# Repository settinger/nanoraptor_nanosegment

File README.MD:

# The NanoRaptor NanoSegment

## Experiments in miniature 7-segment displays

### Sam Ettinger, November 2022

Like many good projects, this started with [a prank tweet:](https://twitter.com/NanoRaptor/status/1483962337334022145)

Like many others, I immediately got sucked into hypotheticals, wondering what it would take to make one of these IRL. Some 0201-sized LEDs in a 7-segment arrangement could fit in an 0805-ish footprint, right?

There are three KiCad projects in the `kicad/` folder:
- `6pin_7seg_0806`, the first version. It's just a panelized PCB with no schematic and some, shall we say, unique features (TODO: explain)
- `6pin_7seg_0806_display_board`. Once the 6-pin 0806 modules are assembled, the modules can be soldered to this board and controlled with an ATtiny84. There are some unused 0805 footprints nearby the modules, which I thought would contribute to it looking like a "real" component.
- `nanoraptor_nanosegment`, my current idea. I want to see if I can fold up an OSH Park flex PCB into a 1208-size footprint with just two pins, like in the original tweet.

TODO: finish this

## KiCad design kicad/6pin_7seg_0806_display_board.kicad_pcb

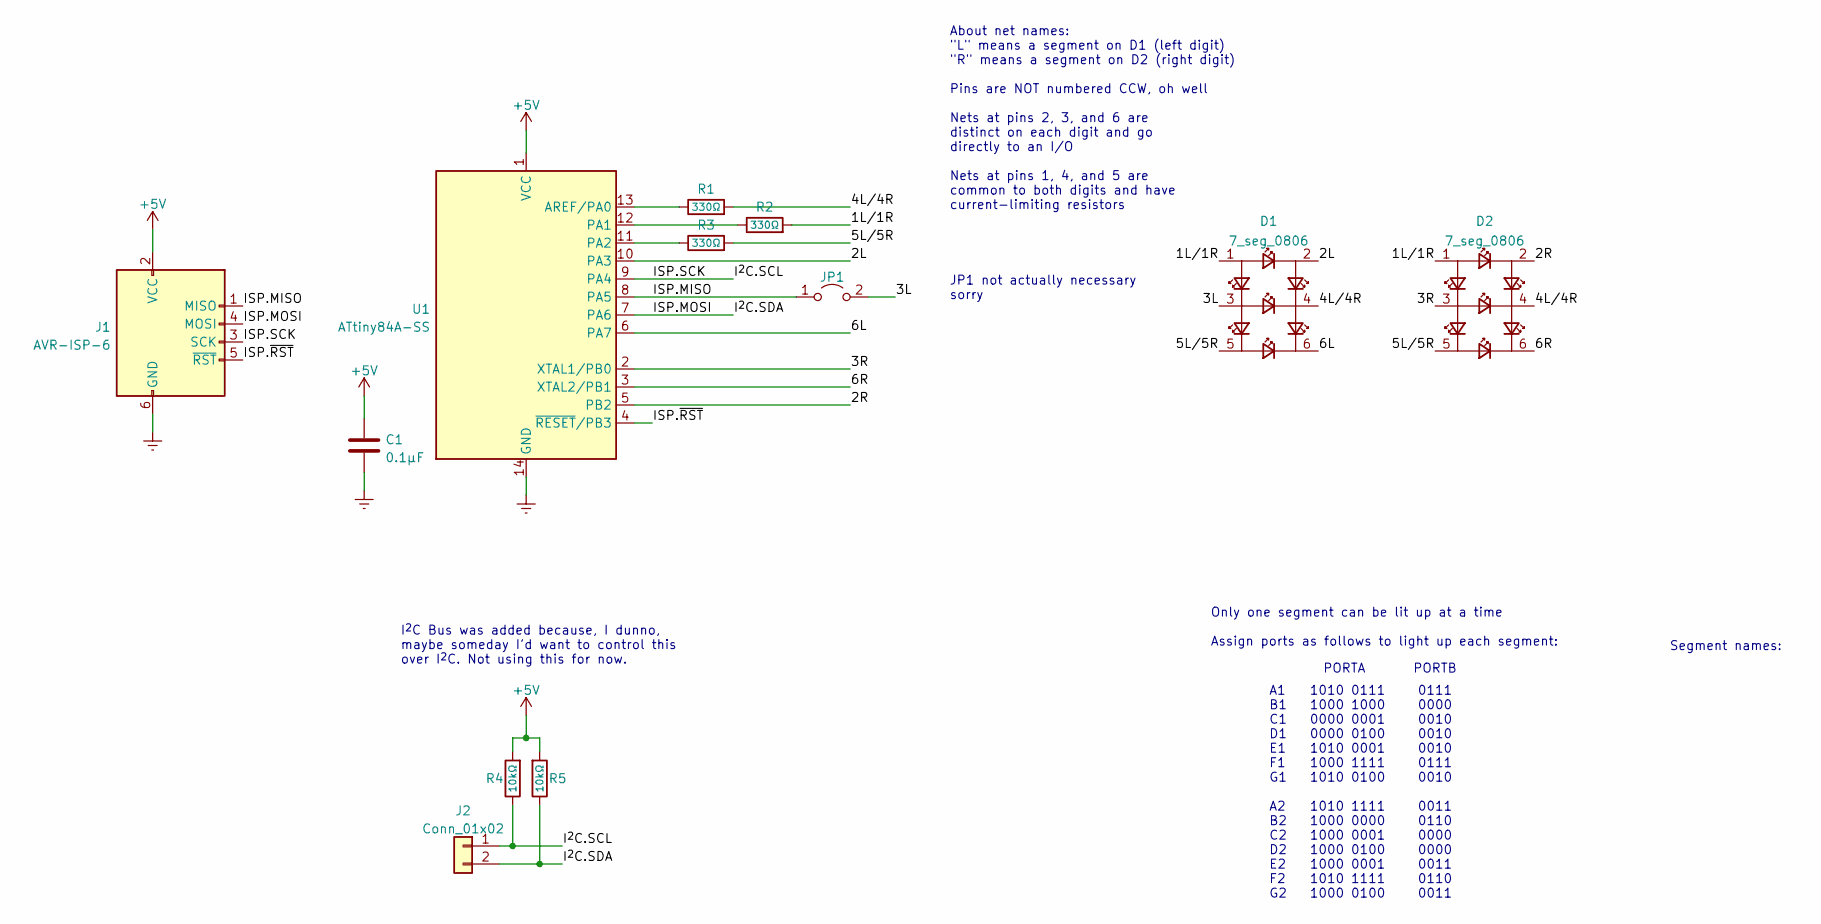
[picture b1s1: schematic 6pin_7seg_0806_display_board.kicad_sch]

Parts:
C1: 0.1μF; C_0805_2012Metric
D1, D2: 7_seg_0806; 7seg_land_pattern
J1: AVR-ISP-6; IDC_header_2x03_P2.54mm_edge-mount
J2: Conn_01x02; PinSocket_1x02_P2.54mm_Vertical
JP1: Jumper_2_Open; SolderJumper-2_P1.3mm_Open_RoundedPad1.0x1.5mm
R1, R2, R3: 330Ω; R_0805_2012Metric
R4, R5: 10kΩ; R_0805_2012Metric
U1: ATtiny84A-SS; SOIC-14_3.9x8.7mm_P1.27mm

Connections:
+5V: C1.1, J1.2 (VCC), R4.2, R5.2, U1.1 (VCC)
/1L/1R: D1.1 (A+F+), D2.1 (A+F+), R2.2
/2L: D1.2 (A-B+), U1.10 (PA3)
/2R: D2.2 (A-B+), U1.5 (PB2)
/3L: D1.3 (E+F-G+), JP1.2 (B)
/3R: D2.3 (E+F-G+), U1.2 (XTAL1/PB0)
/4L/4R: D1.4 (B-C+G-), D2.4 (B-C+G-), R1.2
/5L/5R: D1.5 (D+E-), D2.5 (D+E-), R3.2
/6L: D1.6 (C-D-), U1.6 (PA7)
/6R: D2.6 (C-D-), U1.3 (XTAL2/PB1)
/ISP.MISO: J1.1 (MISO), JP1.1 (A), U1.8 (PA5)
/ISP.MOSI: J1.4 (MOSI), J2.2, R5.1, U1.7 (PA6)
/ISP.SCK: J1.3 (SCK), J2.1, R4.1, U1.9 (PA4)
/ISP.~RST: J1.5 (~RST), U1.4 (~RESET/PB3)
GNDREF: C1.2, J1.6 (GND), U1.14 (GND)
unnamed: R1.1, U1.13 (AREF/PA0)
unnamed: R2.1, U1.12 (PA1)
unnamed: R3.1, U1.11 (PA2)

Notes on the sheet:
1010 0111 1000 1000 0000 0001 0000 0100 1010 0001 1000 1111 1010 0100 1010 1111 1000 0000 1000 0001 1000 0100 1000 0001 1010 1111 1000 0100
JP1 not actually necessary sorry
About net names: "L" means a segment on D1 (left digit) "R" means a segment on D2 (right digit) Pins are NOT numbered CCW, oh well Nets at pins 2, 3, and 6 are distinct on each digit and go directly to an I/O Nets at pins 1, 4, and 5 are common to both digits and have current-limiting resistors
A1 B1 C1 D1 E1 F1 G1 A2 B2 C2 D2 E2 F2 G2
0111 0000 0010 0010 0010 0111 0010 0011 0110 0000 0000 0011 0110 0011
I^{2}C Bus was added because, I dunno, maybe someday I'd want to control this over I^{2}C. Not using this for now.
Only one segment can be lit up at a time Assign ports as follows to light up each segment:
Segment names:
PORTA PORTB

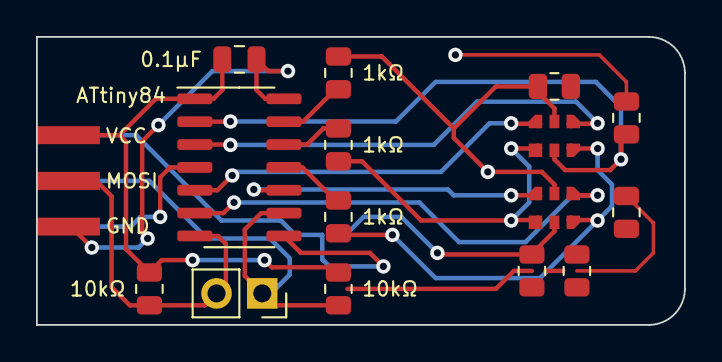
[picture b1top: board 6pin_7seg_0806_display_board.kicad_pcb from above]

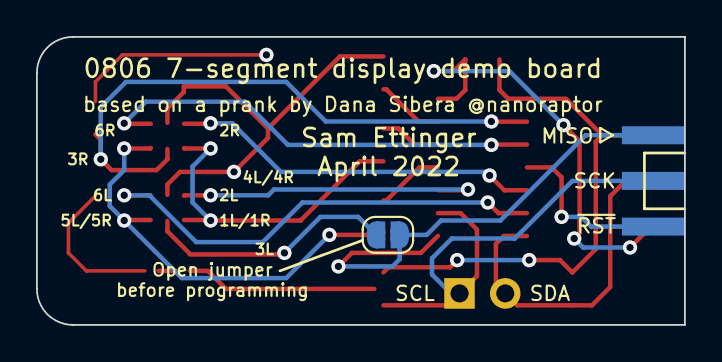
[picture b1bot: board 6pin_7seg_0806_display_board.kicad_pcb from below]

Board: 2 copper layers, 36.0 x 16.0 mm, 12 parts (2 on the bottom side), 18 nets.

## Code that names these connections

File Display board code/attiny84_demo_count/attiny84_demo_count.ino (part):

// ATtiny84 setup for driving those tiny 7-segment surface mount dinguses
// THIS IS NOT GOOD CODE I WAS HUNGOVER AND DOING THIS IN THE MIDDLE OF A CON

#define PIN_1L  1  // Pin 1 of module L is connected to PA1 of the ATtiny84 (denoted "1" in ATtinyCore)
#define PIN_1R PIN_1L
#define PIN_2L  3  // Pin 2 module L: PA3 (attinycore 3)
#define PIN_2R  8  // Pin 2 module R: PB2 (attinycore 8)
#define PIN_3L  5  // Pin 3 module L: PA5 (attinycore 5)
#define PIN_3R 10  // Pin 3 module R: PB0 (attinycore 10)
#define PIN_4L  0  // Pin 4 module L: PA0 (attinycore 0)
#define PIN_4R PIN_4L
#define PIN_5L  2  // Pin 5 module L: PA2 (attinycore 2)
#define PIN_5R PIN_5L
#define PIN_6L  7  // Pin 6 module L: PA7 (attinycore 7)
#define PIN_6R  9  // Pin 6 module R: PB1 (attinycore 9)

#define PORTA_OUTPUT_MASK 0b10101111
#define PORTB_OUTPUT_MASK 0b00000111
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
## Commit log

2022-11-18 Init commit
2022-11-18 Create LICENSE
2022-11-18 attiny84 arduino sketch
